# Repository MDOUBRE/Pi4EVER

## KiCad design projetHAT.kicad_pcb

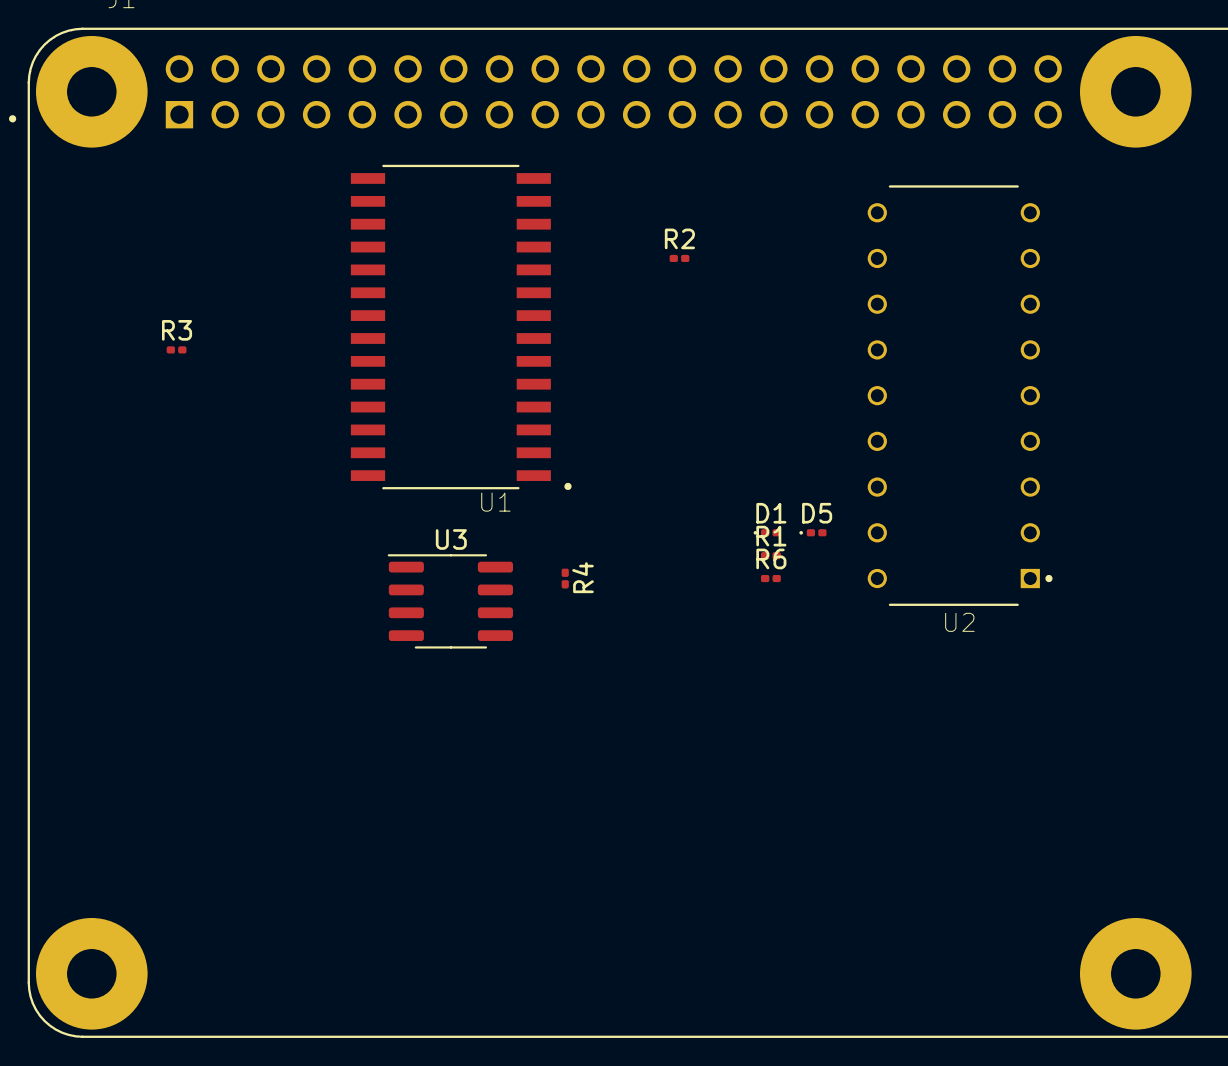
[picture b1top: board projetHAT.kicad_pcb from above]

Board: 2 copper layers, 11 parts (0 on the bottom side), 17 nets, no tracks yet.

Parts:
D1, D5: LED; LED_0201_0603Metric
J1: Raspberry_Pi_2_3; MODULE_RASPBERRY_PI_3_MODEL_B+
R1, R2, R3, R4, R6: R; R_0201_0603Metric
U1: MCP23S17-E_SO; SOIC127P1030X265-28N
U2: ULN2803A; DIP850W46P254L2324H393Q18
U3: AT24CS32-SSHM; SOIC-8_3.9x4.9mm_P1.27mm

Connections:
GND: J1.6, J1.9, J1.14, J1.20, J1.25, J1.30, J1.34, J1.39, R3.2, U1.10, U1.15, U1.16, U1.17, U1.24, U1.25, U1.26, U1.27, U1.28, U2.9, U3.1, U3.2, U3.3, U3.4
unnamed: D1.1, U2.12
unnamed: D1.2, R1.2
unnamed: D5.1, U2.14
unnamed: D5.2, R6.2
unnamed: J1.1, R4.1, U1.9, U1.21, U1.22, U1.23, U3.8
unnamed: J1.2, R1.1, R2.2, R6.1, U2.10
unnamed: J1.7, R2.1, R3.1, U1.18
unnamed: J1.19, U1.13
unnamed: J1.21, U1.14
unnamed: J1.23, U1.12
unnamed: J1.24, U1.11
unnamed: J1.27, U3.6
unnamed: J1.28, U3.5
unnamed: R4.2, U3.7
unnamed: U1.5, U2.5
unnamed: U1.7, U2.7

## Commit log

2021-04-12 Add files via upload
    confiiguration
2021-04-12 Add files via upload
    automation script
